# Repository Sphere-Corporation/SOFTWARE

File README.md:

## SOFTWARE LIBRARY

This repo is a software library of useful items of software that I have found on the internet, or people have directed me towards.

Some of these are tools or software not directly related to the Sphere-1, but are, nonetheless, useful, others are programs directly related to the Sphere-1 which I have used to advance my knowledge and skills in related areas, such as 6800 Assembly language and how the Sphere-1 functions etc.

I do not own ANY of the copyright for these items, nor would I wish to claim any attribution for them, they are simply collected here for convenience.

Licenses for the software contained herein are the responsibility of the creator of that software.

Any modifications that I have done to any code are done in good faith.

### Folders in this repository

The table below contains descriptions and links to the repositories.

|Ref| Description | Location
|----|-----|-----|
|1. | 1702A Reader Programmer | [Local](./1702a-Reader-Programmer/)<br>[Site](https://zeninstruments.blogspot.com/2020/06/diy-1702a-programmer.html)
|2. | SBASM3 Assembler        | [Local](./asm/sbasm3/)<br>[Site](https://www.sbprojects.net/sbasm/)
|3. | 6800 Forth              | [Local](./asm/6800-forth/)<br>[Site](https://sphere.computer/resources/forth/6800_Forth_source.pdf)
|4. | PIE Text Editor |         [Local](./asm/PIE/)<br>[Site](https://sphere.computer/resources/pie_editor_source.asm)
|5. | Cassette Firmware Source |[Local](./asm/TAPE/)<br>[Site](https://sphere.computer/resources/pie_editor_source.asm)
|6. | PDS-V3N firmware source code |[Local](./firmware/)<br>[Site](https://sphere.computer/resources/firmware/PDS-V3N.a68)
|7. | 1702A-Programmer |[Local](./kicad-1702a-programmer/)

### Note:
Whilst I do not wish to repeat a "collection" of Sphere-1 resources (for that, you should seek [Sphere Resources](https://sphere.computer/resources.html) by Ben Zotto, I did want to collect some useful stuff to me together as a convenience.

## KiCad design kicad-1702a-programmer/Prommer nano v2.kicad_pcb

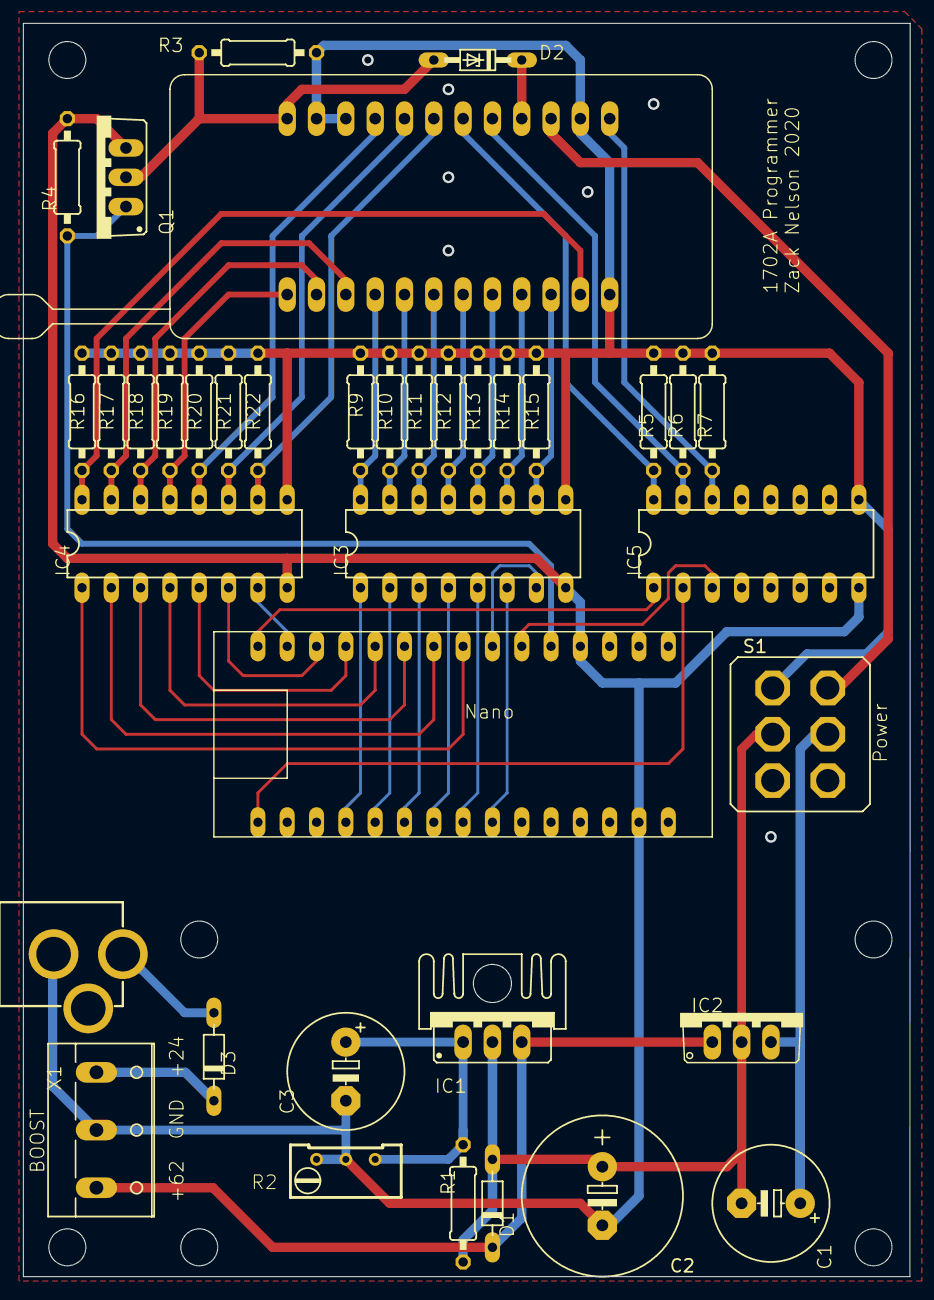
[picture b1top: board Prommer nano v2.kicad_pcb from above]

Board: 2 copper layers, 76.8 x 108.6 mm, 46 parts (0 on the bottom side), 46 nets.

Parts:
@HOLE0, @HOLE1, @HOLE2, @HOLE3, @HOLE4, @HOLE5, @HOLE6: (no value)
C1: 220uf; E5-10,5
C2: 220uf/100v; E5-13
C3: 22uf; E5-10,5
D1, D3: 1N4001; D-7.5
D2: 10V; DO34Z7
IC1: TL783; 317TS
IC2: 7812TV; TO220V
IC3, IC4, IC5: ULN2003AN; DIL16
J1: POWER_JACK; POWER_JACK_PTH
KK1: SK95-2M3
Q1: IRF520; TO220BV
R1: 220Ω; 0207_10
R2: 10k; RTRIM64W
R3, R5, R6, R7, R9, R10, R11, R12, R13, R14, R15, R16, R17, R18, R19, R20, R21, R22: 6.8k; 0207_10
R4: 1k; 0207_10
S1: 320-938
U1: 1702ZIF; ZIF24
U$1: NANO
X1: W237-103

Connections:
+24V: D3.C, X1.1
+47V: IC3.9, IC4.9, IC5.9, R3.2, R5.1, R6.1, R7.1, R9.1, R10.1, R11.1, R12.1, R13.1, R14.1, R15.1, R16.1, R17.1, R18.1, R19.1, R20.1, R21.1, R22.1, S1.1, U1.12, U1.14, U1.22, U1.23
+59V: C1.+, IC2.3, S1.5
A0: IC4.15, R17.2, U1.3
A1: IC4.14, R18.2, U1.2
A2: IC4.13, R19.2, U1.1
A3: IC4.12, R20.2, U1.21
A4: IC4.11, R21.2, U1.20
A5: IC4.10, R22.2, U1.19
A6: IC5.16, R5.2, U1.18
A7: IC5.15, R6.2, U1.17
AA0: IC3.1, U$1.A0
AA1: IC3.2, U$1.A1
AA2: IC3.3, U$1.A2
AA3: IC3.4, U$1.A3
AA4: IC3.5, U$1.A4
AA5: IC3.6, U$1.A5
AD2: Q1.G, R4.1, U$1.D2
AD3: IC5.3, U$1.D3
AD4: IC3.7, U$1.D4
AD5: IC4.1, U$1.D5
AD6: IC4.2, U$1.D6
AD7: IC4.3, U$1.D7
AD8: IC4.4, U$1.D8
AD9: IC4.5, U$1.D9
AD10: IC4.6, U$1.D10
AD11: IC4.7, U$1.D11
AD12: IC5.1, U$1.D12
AD13: IC5.2, U$1.D13
GND: C2.-, C3.-, IC3.8, IC4.8, IC5.8, J1.GND, Q1.S, R2.2, R2.3, R4.2, U$1.GND, U$1.GND1, X1.2
unnamed: D1.C, IC1.3, IC2.1, X1.3
unnamed: C3.+, IC1.1, R1.1, R2.1
unnamed: D2.C, U1.16
unnamed: D2.A, Q1.D, R3.1, U1.24
unnamed: C1.-, C2.+, D1.A, IC1.2, IC2.2, R1.2, S1.2
unnamed: D3.A, J1.PWR
unnamed: S1.4, U1.15
O0: IC3.16, R9.2, U1.4
O1: IC3.15, R10.2, U1.5
O2: IC3.14, R11.2, U1.6
O3: IC3.13, R12.2, U1.7
O4: IC3.12, R13.2, U1.8
O5: IC3.11, R14.2, U1.9
O6: IC3.10, R15.2, U1.10
O7: IC4.16, R16.2, U1.11
VPP: IC5.14, R7.2, U1.13

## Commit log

2023-09-28 Changes to TTT game
    Last upload of these changes prior to migration to independent submodule.
2023-09-28 Removed TTT Game as migrated to own submodule now
2024-12-29 Updated README file
2024-12-29 Further readme updates
2024-12-29 Reinitialised repo
2024-12-29 Rebasedlined
